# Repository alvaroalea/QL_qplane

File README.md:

# QPLANE - SINCLAIR QL Backplane port expansion.

(C) 2023 Alvaro Alea Fernandez

License under: CERN Open Hardware Licence Version 2 - Strongly Reciprocal

https://ohwr.org/cern_ohl_s_v2.txt

This board has been reverse engineered from pictures freely available on internet.

THIS BOARD HAS NOT BEEN TESTED!! Use at your own risk.

## Information

This backplane is intended for install the QL main board in a PC AT case.

* Provide 3 expansion slot, this slot has the oposite direction of insert.
* Get energy from tipical AT power supply, for that is need to remove the regulator in the QL
* This cause that microdrive do not work, 
* This also cause that board of expansion need to be modified to adapt to the new voltages.

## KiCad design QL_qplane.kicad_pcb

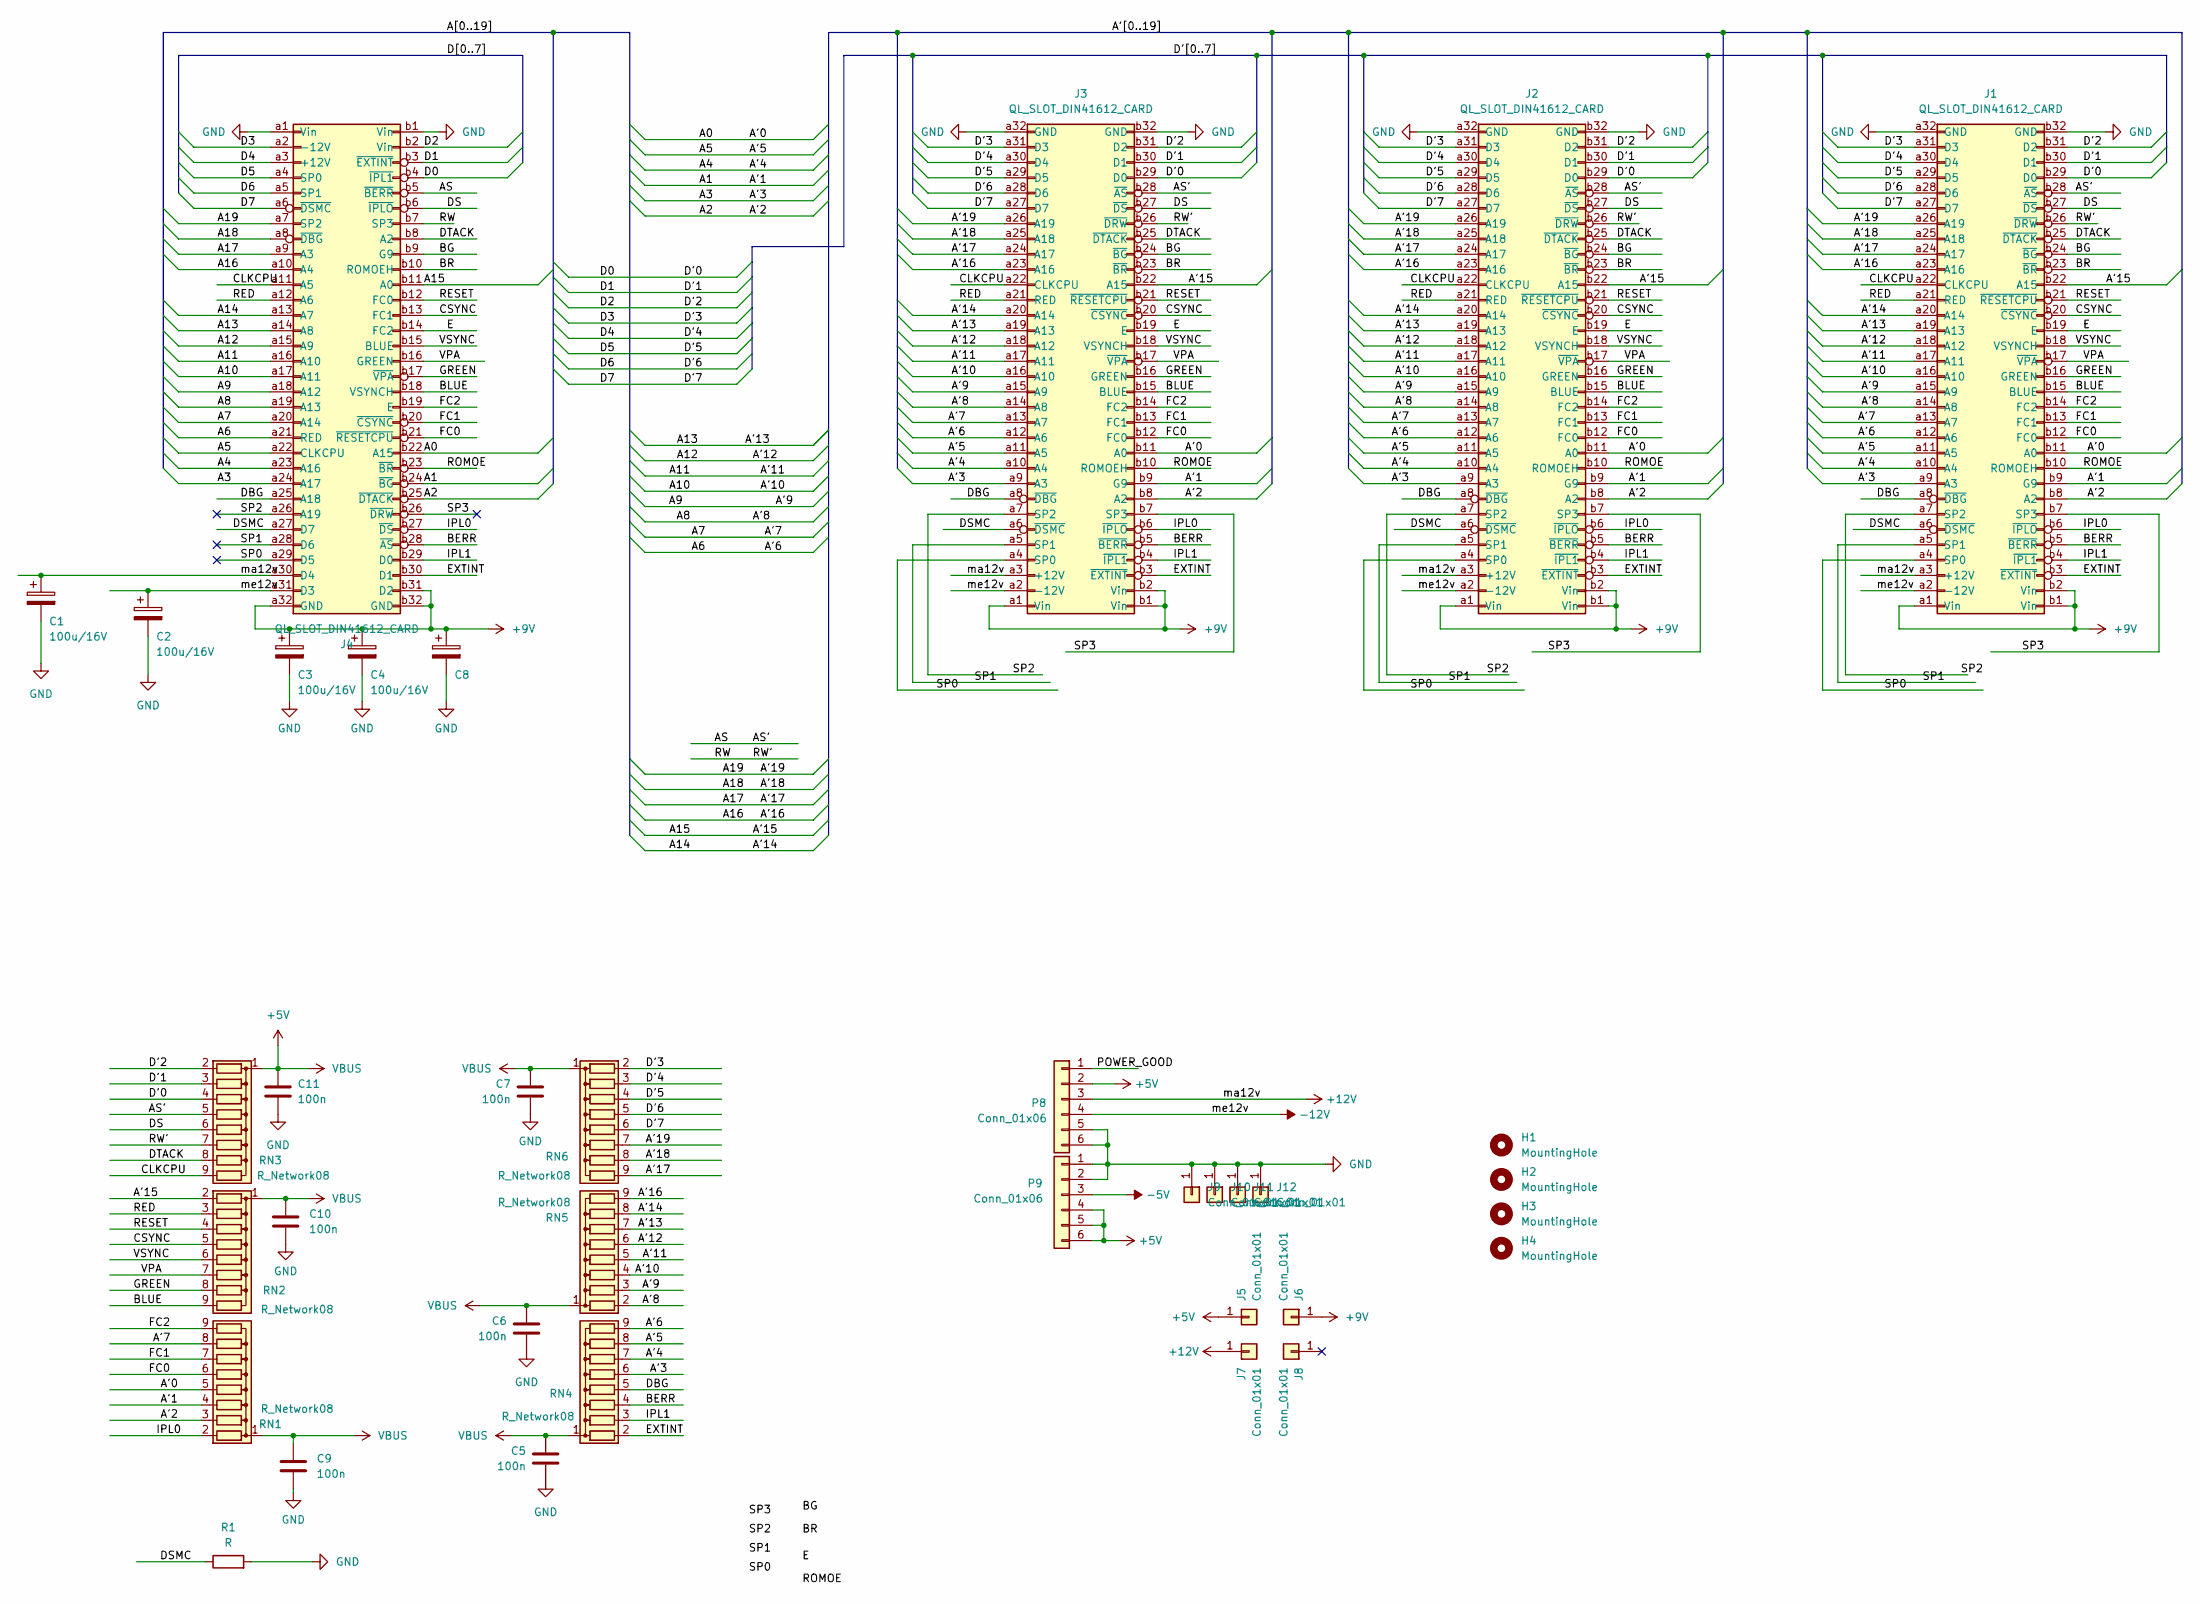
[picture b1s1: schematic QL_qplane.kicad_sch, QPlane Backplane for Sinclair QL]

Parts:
C1, C2, C3, C4, C8: 100u/16V; CP_Radial_D5.0mm_P2.50mm
C5, C6, C7, C9, C10, C11: 100n; C_Disc_D5.0mm_W2.5mm_P2.50mm
H1, H2, H3, H4: MountingHole; MountingHole_3.2mm_M3_ISO7380
J1, J2, J3: QL_SLOT_DIN41612_CARD; DIN41612_Q_2x32_Male_Vertical_THT
J4: QL_SLOT_DIN41612_CARD; DIN41612_B_2x32_Female_Vertical_THT
J5, J6, J7, J8: Conn_01x01; Pin_D1.3mm_L11.0mm
J9, J10, J11, J12: Conn_01x01; Pin_D1.0mm_L10.0mm
P8, P9: Conn_01x06; Molex_15-48-106_1x06_P3.96mm_Vertical
R1: R; R_Axial_DIN0204_L3.6mm_D1.6mm_P11.17mm_Horizontal
RN1, RN2, RN3, RN4, RN5, RN6: R_Network08; R_Array_SIP9

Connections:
+5V: C5.1, C6.1, C7.1, C9.2, C10.2, C11.1, J5.1, P8.2, P9.4, P9.5, P9.6, RN1.1 (common), RN2.1 (common), RN3.1 (common), RN4.1 (common), RN5.1 (common), RN6.1 (common)
+9V: C3.1, C4.1, C8.1, J1.a1 (Vin), J1.b1 (Vin), J1.b2 (Vin), J2.a1 (Vin), J2.b1 (Vin), J2.b2 (Vin), J3.a1 (Vin), J3.b1 (Vin), J3.b2 (Vin), J4.a32 (GND), J4.b31 (D2), J4.b32 (GND), J6.1
+12V: C1.1, J1.a3 (+12V), J2.a3 (+12V), J3.a3 (+12V), J4.a30 (D4), J7.1, P8.3
-5V: P9.3
-12V: C2.1, J1.a2 (-12V), J2.a2 (-12V), J3.a2 (-12V), J4.a31 (D3), P8.4
/A0: J1.b11 (A0), J2.b11 (A0), J3.b11 (A0), J4.b22 (A15), RN1.5 (R4)
/A1: J1.b9 (G9), J2.b9 (G9), J3.b9 (G9), J4.b24 (~BG), RN1.4 (R3)
/A2: J1.b8 (A2), J2.b8 (A2), J3.b8 (A2), J4.b25 (~DTACK), RN1.3 (R2)
/A3: J1.a9 (A3), J2.a9 (A3), J3.a9 (A3), J4.a24 (A17), RN4.6 (R5)
/A4: J1.a10 (A4), J2.a10 (A4), J3.a10 (A4), J4.a23 (A16), RN4.7 (R6)
/A5: J1.a11 (A5), J2.a11 (A5), J3.a11 (A5), J4.a22 (CLKCPU), RN4.8 (R7)
/A6: J1.a12 (A6), J2.a12 (A6), J3.a12 (A6), J4.a21 (RED), RN4.9 (R8)
/A7: J1.a13 (A7), J2.a13 (A7), J3.a13 (A7), J4.a20 (A14), RN1.8 (R7)
/A8: J1.a14 (A8), J2.a14 (A8), J3.a14 (A8), J4.a19 (A13), RN5.2 (R1)
/A9: J1.a15 (A9), J2.a15 (A9), J3.a15 (A9), J4.a18 (A12), RN5.3 (R2)
/A10: J1.a16 (A10), J2.a16 (A10), J3.a16 (A10), J4.a17 (A11), RN5.4 (R3)
/A11: J1.a17 (A11), J2.a17 (A11), J3.a17 (A11), J4.a16 (A10), RN5.5 (R4)
/A12: J1.a18 (A12), J2.a18 (A12), J3.a18 (A12), J4.a15 (A9), RN5.6 (R5)
/A13: J1.a19 (A13), J2.a19 (A13), J3.a19 (A13), J4.a14 (A8), RN5.7 (R6)
/A14: J1.a20 (A14), J2.a20 (A14), J3.a20 (A14), J4.a13 (A7), RN5.8 (R7)
/A15: J1.b22 (A15), J2.b22 (A15), J3.b22 (A15), J4.b11 (A0), RN2.2 (R1)
/A16: J1.a23 (A16), J2.a23 (A16), J3.a23 (A16), J4.a10 (A4), RN5.9 (R8)
/A17: J1.a24 (A17), J2.a24 (A17), J3.a24 (A17), J4.a9 (A3), RN6.9 (R8)
/A18: J1.a25 (A18), J2.a25 (A18), J3.a25 (A18), J4.a8 (~DBG), RN6.8 (R7)
/A19: J1.a26 (A19), J2.a26 (A19), J3.a26 (A19), J4.a7 (SP2), RN6.7 (R6)
/AS: J1.b28 (~AS), J2.b28 (~AS), J3.b28 (~AS), J4.b5 (~BERR), RN3.5 (R4)
/BERR: J1.b5 (~BERR), J2.b5 (~BERR), J3.b5 (~BERR), J4.b28 (~AS), RN4.4 (R3)
/BG: J1.b24 (~BG), J2.b24 (~BG), J3.b24 (~BG), J4.b9 (G9)
/BLUE: J1.b15 (BLUE), J2.b15 (BLUE), J3.b15 (BLUE), J4.b18 (VSYNCH), RN2.9 (R8)
/BR: J1.b23 (~BR), J2.b23 (~BR), J3.b23 (~BR), J4.b10 (ROMOEH)
/CLKCPU: J1.a22 (CLKCPU), J2.a22 (CLKCPU), J3.a22 (CLKCPU), J4.a11 (A5), RN3.9 (R8)
/CSYNC: J1.b20 (~CSYNC), J2.b20 (~CSYNC), J3.b20 (~CSYNC), J4.b13 (FC1), RN2.5 (R4)
/D0: J1.b29 (D0), J2.b29 (D0), J3.b29 (D0), J4.b4 (~IPL1), RN3.4 (R3)
/D1: J1.b30 (D1), J2.b30 (D1), J3.b30 (D1), J4.b3 (~EXTINT), RN3.3 (R2)
/D2: J1.b31 (D2), J2.b31 (D2), J3.b31 (D2), J4.b2 (Vin), RN3.2 (R1)
/D3: J1.a31 (D3), J2.a31 (D3), J3.a31 (D3), J4.a2 (-12V), RN6.2 (R1)
/D4: J1.a30 (D4), J2.a30 (D4), J3.a30 (D4), J4.a3 (+12V), RN6.3 (R2)
/D5: J1.a29 (D5), J2.a29 (D5), J3.a29 (D5), J4.a4 (SP0), RN6.4 (R3)
/D6: J1.a28 (D6), J2.a28 (D6), J3.a28 (D6), J4.a5 (SP1), RN6.5 (R4)
/D7: J1.a27 (D7), J2.a27 (D7), J3.a27 (D7), J4.a6 (~DSMC), RN6.6 (R5)
/DBG: J1.a8 (~DBG), J2.a8 (~DBG), J3.a8 (~DBG), J4.a25 (A18), RN4.5 (R4)
/DS: J1.b27 (~DS), J2.b27 (~DS), J3.b27 (~DS), J4.b6 (~IPLO), RN3.6 (R5)
/DSMC: J1.a6 (~DSMC), J2.a6 (~DSMC), J3.a6 (~DSMC), J4.a27 (D7), R1.1
/DTACK: J1.b25 (~DTACK), J2.b25 (~DTACK), J3.b25 (~DTACK), J4.b8 (A2), RN3.8 (R7)
/E: J1.b19 (E), J2.b19 (E), J3.b19 (E), J4.b14 (FC2)
/EXTINT: J1.b3 (~EXTINT), J2.b3 (~EXTINT), J3.b3 (~EXTINT), J4.b30 (D1), RN4.2 (R1)
/FC0: J1.b12 (FC0), J2.b12 (FC0), J3.b12 (FC0), J4.b21 (~RESETCPU), RN1.6 (R5)
/FC1: J1.b13 (FC1), J2.b13 (FC1), J3.b13 (FC1), J4.b20 (~CSYNC), RN1.7 (R6)
/FC2: J1.b14 (FC2), J2.b14 (FC2), J3.b14 (FC2), J4.b19 (E), RN1.9 (R8)
/GREEN: J1.b16 (GREEN), J2.b16 (GREEN), J3.b16 (GREEN), J4.b17 (~VPA), RN2.8 (R7)
/IPL0: J1.b6 (~IPLO), J2.b6 (~IPLO), J3.b6 (~IPLO), J4.b27 (~DS), RN1.2 (R1)
/IPL1: J1.b4 (~IPL1), J2.b4 (~IPL1), J3.b4 (~IPL1), J4.b29 (D0), RN4.3 (R2)
/POWER_GOOD: P8.1
/RED: J1.a21 (RED), J2.a21 (RED), J3.a21 (RED), J4.a12 (A6), RN2.3 (R2)
/RESET: J1.b21 (~RESETCPU), J2.b21 (~RESETCPU), J3.b21 (~RESETCPU), J4.b12 (FC0), RN2.4 (R3)
/ROMOE: J1.b10 (ROMOEH), J2.b10 (ROMOEH), J3.b10 (ROMOEH), J4.b23 (~BR)
/RW: J1.b26 (~DRW), J2.b26 (~DRW), J3.b26 (~DRW), J4.b7 (SP3), RN3.7 (R6)
/SP0: J1.a4 (SP0), J2.a4 (SP0), J3.a4 (SP0), J4.a29 (D5)
/SP1: J1.a5 (SP1), J2.a5 (SP1), J3.a5 (SP1), J4.a28 (D6)
/SP2: J1.a7 (SP2), J2.a7 (SP2), J3.a7 (SP2), J4.a26 (A19)
/SP3: J1.b7 (SP3), J2.b7 (SP3), J3.b7 (SP3), J4.b26 (~DRW)
/VPA: J1.b17 (~VPA), J2.b17 (~VPA), J3.b17 (~VPA), J4.b16 (GREEN), RN2.7 (R6)
/VSYNC: J1.b18 (VSYNCH), J2.b18 (VSYNCH), J3.b18 (VSYNCH), J4.b15 (BLUE), RN2.6 (R5)
GND: C1.2, C2.2, C3.2, C4.2, C5.2, C6.2, C7.2, C8.2, C9.1, C10.1, C11.2, J1.a32 (GND), J1.b32 (GND), J2.a32 (GND), J2.b32 (GND), J3.a32 (GND), J3.b32 (GND), J4.a1 (Vin), J4.b1 (Vin), J9.1, J10.1, J11.1, J12.1, P8.5, P8.6, P9.1, P9.2, R1.2

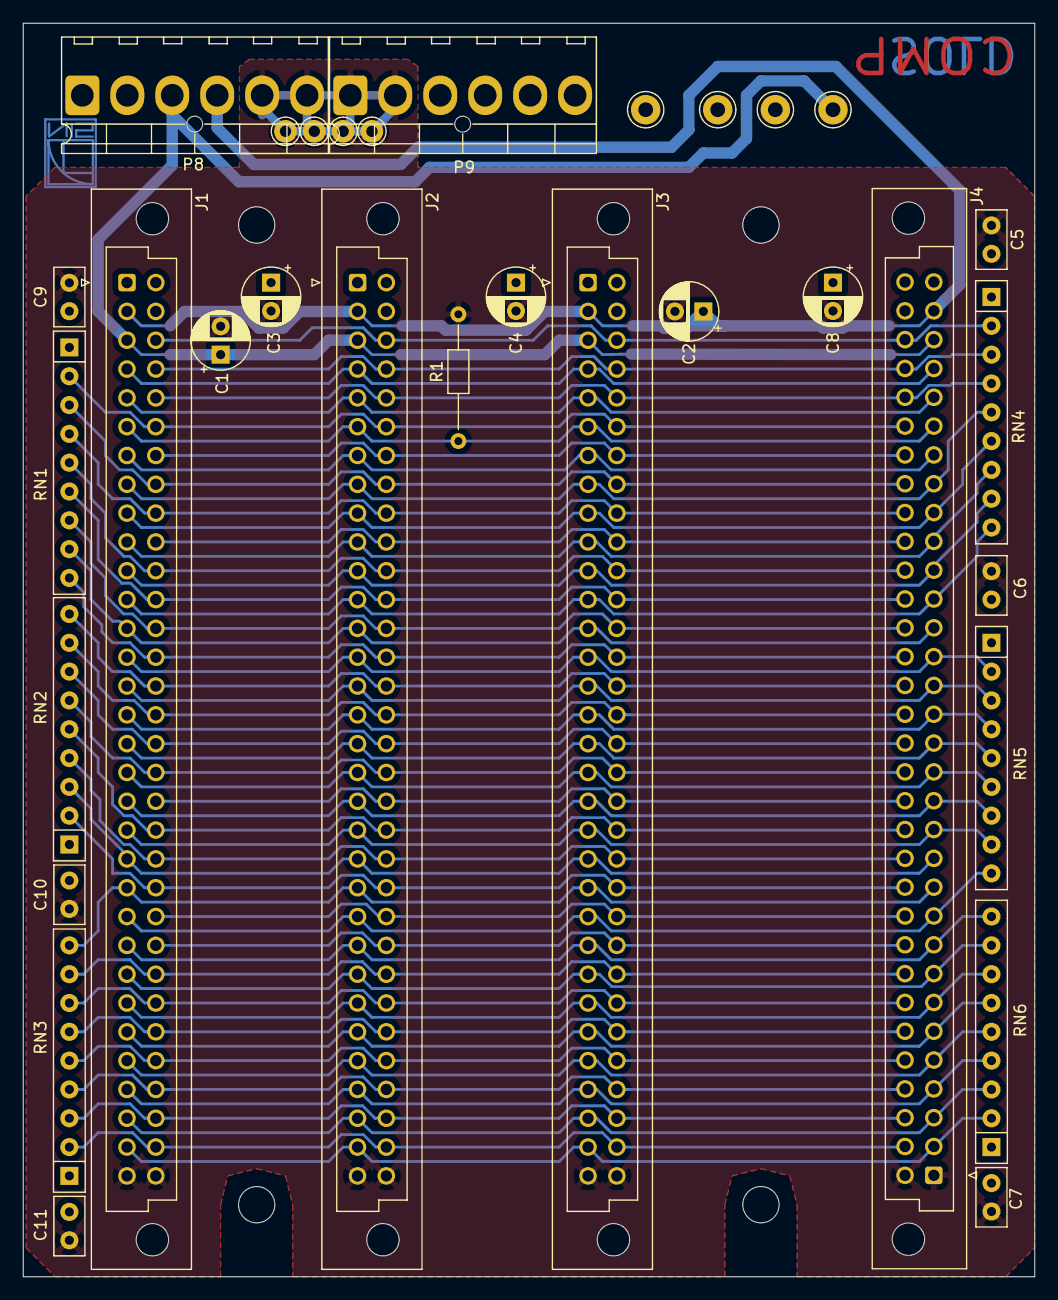
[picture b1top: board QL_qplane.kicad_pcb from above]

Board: 2 copper layers, 89.2 x 110.5 mm, 36 parts (0 on the bottom side), 62 nets.

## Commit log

2023-11-11 Initial

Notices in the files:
QL_qplane.kicad_pcb:
(C) 2023 Alvaro Alea Fdz.
Under License
Licensed under Cern OHL-S
